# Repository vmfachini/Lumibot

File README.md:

# Lumibot
Desenvolvimento de um Hardware Livre, com uso de energia limpa, baseado no micro:bit para criar robôs móveis acessíveis, promovendo ensino de robótica, pensamento computacional e sustentabilidade no Brasil.

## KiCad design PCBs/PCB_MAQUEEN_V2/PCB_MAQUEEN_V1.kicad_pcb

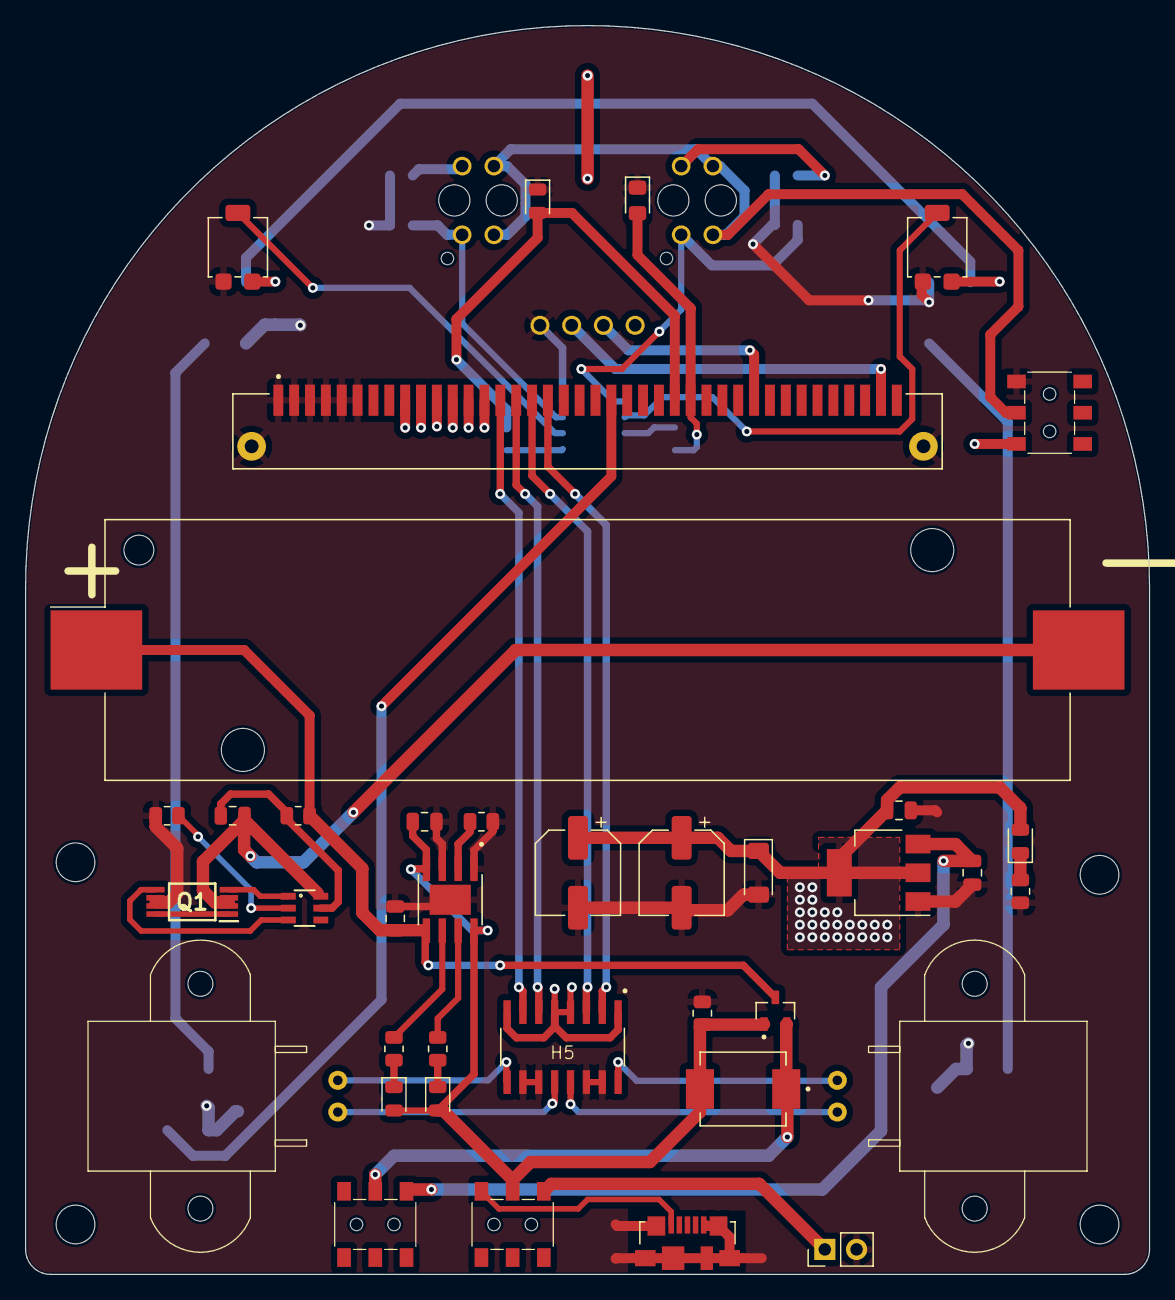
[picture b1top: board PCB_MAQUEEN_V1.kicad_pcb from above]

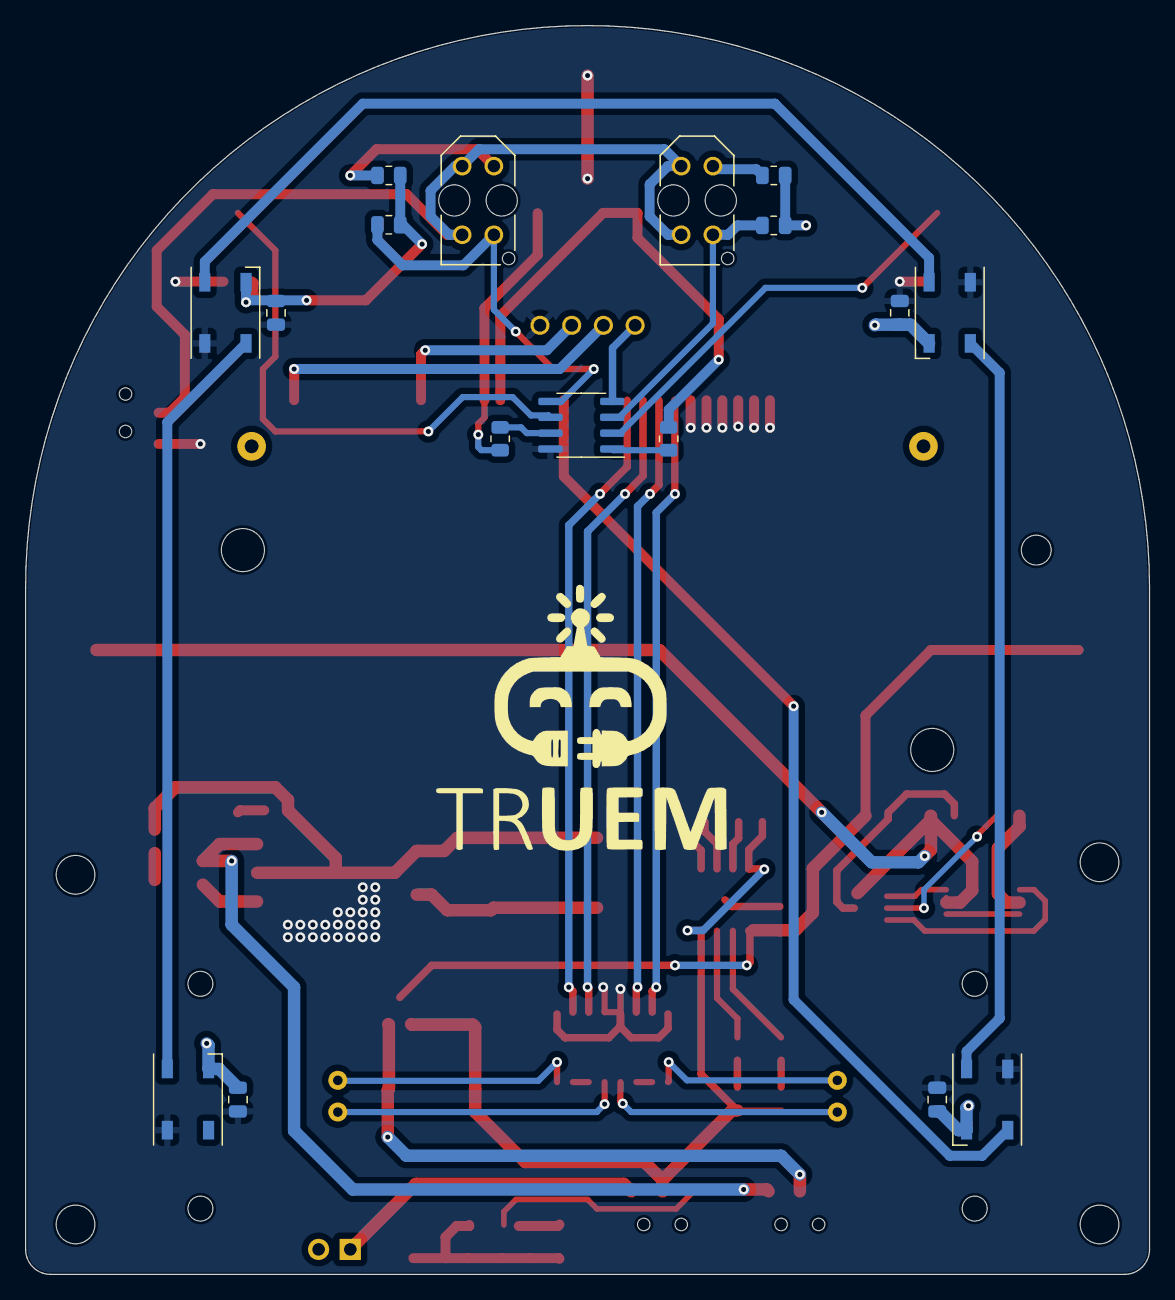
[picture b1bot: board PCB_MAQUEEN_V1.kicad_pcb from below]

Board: 2 copper layers, 90.0 x 100.0 mm, 61 parts (17 on the bottom side), 45 nets.

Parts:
BT1: Battery; BatteryHolder_Keystone_1042_1x18650
C1, C2, C4, C5: 10uF; C_0805_2012Metric
C3, C8, C9, C10, C11: 100nF; C_0805_2012Metric
C6, C7: C_Pol; CP_Elec_6.3x5.9
D1, D4: LED RED; LED_0805_2012Metric
D2: LED GREEN; LED_0805_2012Metric
D3: SS34
D5: BZV55B5V1; D_MiniMELF
D9: LED; LED_0805_2012Metric
D12: LED; LED_0805_2012Metric_Pad1.15x1.40mm_HandSolder
D13, D14, D15, D16: WS2812B; LED_WS2812B_PLCC4_5.0x5.0mm_P3.2mm
H1, H2, H3, H4: MountingHole; Espacador
H5: MountingHole; Painel_solar
J1: USB_B_Micro; USB_Micro-B_Molex_47346-0001
J2: MIC127-140-A01; DONGGUAN_MIC127-140-A01
J3: MOT_1; Motor_N20_com_case
J5: MOT_2; Motor_N20_com_case
J7: Painel solar; PinHeader_1x02_P2.54mm_Vertical
Q1: FS8205A
Q2: DMP1045U
R1: 100; R_0805_2012Metric
R2, R4, R5, R7: 1K; R_0805_2012Metric
R3: 1.2K; R_0805_2012Metric
R6: 10K; R_0805_2012Metric
R10, R13: 200; R_0805_2012Metric
R11, R14: 10k; R_0805_2012Metric
R12, R15: 330; R_0805_2012Metric
RV1, RV2: POT. 10K; Potentiometer_Bourns_3314G_Vertical
SW1: ON/OFF; SW_DESLIZANTE
SW2: ON/OFF LINE FOLLOW; SW_DESLIZANTE
SW3: BAT/PAINEL; SW_DESLIZANTE
U1: DW01A
U2: TP4056
U3: LM1117MP-3.3; SOT-223-3_TabPin2
U4: MX1508
U5: LM358; SOIC-8_3.9x4.9mm_P1.27mm
U6: HC-SR04; XCVR_HC-SR04
U7, U8: TCRT5000; OPTO_TCRT5000

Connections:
+3V3: C5.1, C6.1, C7.1, C8.1, C9.1, C10.1, C11.1, D4.2 (A), D5.1 (K), D13.1 (VDD), D14.1 (VDD), D15.1 (VDD), D16.1 (VDD), J2.9 (+3V3_9), J2.10 (+3V3_10), J2.11 (+3V3_11), J2.12 (+3V3_12), J2.13 (+3V3_13), J2.14 (+3V3_14), RV1.1, RV2.1, SW2.3 (C), U3.2 (VO), U4.1 (VCC_1), U4.4 (VDD_1), U4.5 (VCC_2), U4.8 (VDD_2), U5.8 (V+), U6.1 (VCC)
+BATT: BT1.1 (+), C2.1, Q2.3, R1.1, U2.5 (BAT)
-BATT: BT1.2 (-), C3.2, Q1.2 (S1_1), Q1.3 (S1_2), U1.6 (GND)
/Digital/ECHO: J2.39 (P0_4/AIN), U6.3 (ECHO)
/Digital/LED_DIN: D13.4 (DIN), J2.22 (P2_4/AIN)
/Digital/LineFollow1: D9.2 (A), J2.26 (P9/LED_COL_7), R12.2
/Digital/LineFollow2: D12.2 (A), J2.27 (P8), R15.2
/Digital/TRIG: J2.31 (P1_4/AIN), U6.2 (TRIG)
/Motores/OUT_A1: J3.1, U4.16 (OUT_A1)
/Motores/OUT_A2: J5.1, U4.12 (OUT_A2)
/Motores/OUT_B1: J3.2, U4.13 (OUT_B1)
/Motores/OUT_B2: J5.2, U4.9 (OUT_B2)
/Power/Vin: C4.1, SW1.1 (A), U3.3 (VI)
GND: C1.2, C2.2, C4.2, C5.2, C6.2, C7.2, C8.2, C9.2, C10.2, C11.2, D5.2 (A), D9.1 (K), D12.1 (K), D13.3 (VSS), D14.3 (VSS), D15.3 (VSS), D16.3 (VSS), J1.5 (GND), J1.6 (Shield), J2.1 (GND_1), J2.2 (GND_2), J2.3 (GND_3), J2.4 (GND_4), J2.5 (GND_5), J2.6 (GND_6), J2.S1 (SHIELD), J2.S2 (SHIELD), J7.2, Q1.6 (S2_1), Q1.7 (S2_2), R2.2, R3.1, R6.2, R7.2, R10.2, R11.2, R13.2, R14.2, RV1.3, RV2.3, SW2.1 (A), U2.1 (TEMP), U2.3 (GND), U2.9 (EP), U3.1 (GND), U4.10 (AGND_2), U4.11 (PGND_2), U4.14 (AGND_1), U4.15 (PGND_1), U5.4 (V-), U6.4 (GND)
IN_A1: J2.18 (P13/SCL), U4.2 (IN_A1)
IN_A2: J2.16 (P15/MOSI), U4.6 (IN_A2)
IN_B1: J2.17 (P14/MISO), U4.3 (IN_B1)
IN_B2: J2.15 (P16), U4.7 (IN_B2)
unnamed: D1.1 (K), R4.2
unnamed: D2.1 (K), R5.2
unnamed: D4.1 (K), R7.1
unnamed: D13.2 (DOUT), D14.4 (DIN)
unnamed: D14.2 (DOUT), D15.4 (DIN)
unnamed: D15.2 (DOUT), D16.4 (DIN)
unnamed: J1.1 (VBUS), SW3.3 (C)
unnamed: J7.1, SW3.1 (A)
unnamed: Q1.1 (D12_1), Q1.8 (D12_2)
unnamed: Q1.4 (G1), U1.1 (OD)
unnamed: Q1.5 (G2), U1.3 (OC)
unnamed: R10.1, U8.CATH
unnamed: R12.1, U5.1
unnamed: R13.1, U7.CATH
unnamed: R15.1, U5.7
unnamed: D3.C, Q2.2, SW1.2 (B)
unnamed: SW2.2 (B), U7.A, U7.COLL, U8.A, U8.COLL
unnamed: R2.1, U1.2 (CS)
unnamed: C3.1, R1.2, U1.5 (VCC)
unnamed: R3.2, U2.2 (PROG)
unnamed: R4.1, U2.7 (~CHRG)
unnamed: R5.1, U2.6 (~STDBY)
unnamed: R11.1, U5.3 (+), U8.E
unnamed: RV1.2, U5.2 (-)
unnamed: R14.1, U5.5 (+), U7.E
unnamed: RV2.2, U5.6 (-)
VBUS: C1.1, D1.2 (A), D2.2 (A), D3.A, Q2.1, R6.1, SW3.2 (B), U2.4 (VCC), U2.8 (CE)

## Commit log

2024-11-19 commit inicial
    Envio dos arquivos das versões 1 e 2 da PCB do Lumibot
